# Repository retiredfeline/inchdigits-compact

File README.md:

# 1 inch tall 4 digit 7 segment display driven by TM1637 - compact version

These are the Kicad design files for my Hackaday project [Inch Digits](https://hackaday.io/project/169179-inch-digits)

## Versioning

November 2022

## Notes

## Authors

* **Ken Yap**

## License

See the [LICENSE](LICENSE.md) file for license rights and limitations (MIT).

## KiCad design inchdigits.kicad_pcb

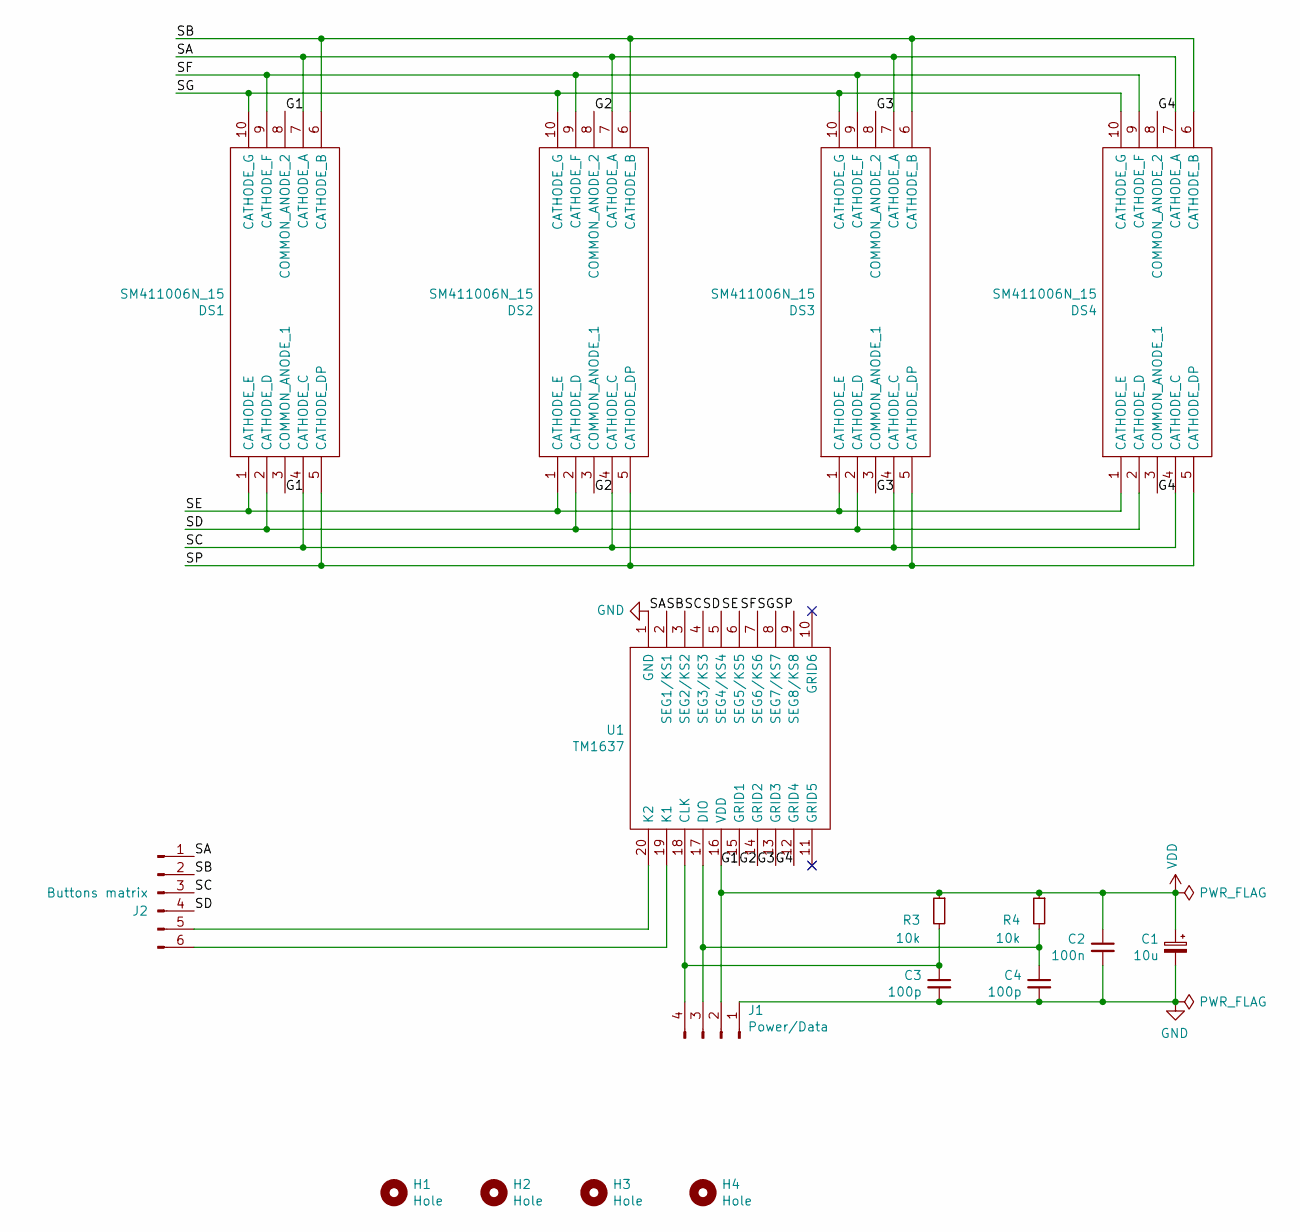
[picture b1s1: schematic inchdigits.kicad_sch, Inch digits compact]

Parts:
C1: 10u; C_0805_2012Metric_Pad1.18x1.45mm_HandSolder
C2: 100n; C_0805_2012Metric_Pad1.18x1.45mm_HandSolder
C3, C4: 100p; C_0805_2012Metric_Pad1.18x1.45mm_HandSolder
DS1, DS2, DS3, DS4: SM411006N_15; DIPS3048W51P254L2400H1075Q10N; Manufacturer_Part_Number SM411006N/15
H1, H2, H3, H4: Hole; MountingHole_3.5mm_Pad
J1: Power/Data; PinHeader_1x04_P2.54mm_Horizontal
J2: Buttons matrix; PinHeader_1x06_P2.54mm_Horizontal
R3, R4: 10k; R_0805_2012Metric_Pad1.20x1.40mm_HandSolder
U1: TM1637; SO-20_12.8x7.5mm_P1.27mm; Manufacturer_Part_Number TM1637

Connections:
/G1: DS1.3 (COMMON_ANODE_1), DS1.8 (COMMON_ANODE_2), U1.15 (GRID1)
/G2: DS2.3 (COMMON_ANODE_1), DS2.8 (COMMON_ANODE_2), U1.14 (GRID2)
/G3: DS3.3 (COMMON_ANODE_1), DS3.8 (COMMON_ANODE_2), U1.13 (GRID3)
/G4: DS4.3 (COMMON_ANODE_1), DS4.8 (COMMON_ANODE_2), U1.12 (GRID4)
/SA: DS1.7 (CATHODE_A), DS2.7 (CATHODE_A), DS3.7 (CATHODE_A), DS4.7 (CATHODE_A), J2.1, U1.2 (SEG1/KS1)
/SB: DS1.6 (CATHODE_B), DS2.6 (CATHODE_B), DS3.6 (CATHODE_B), DS4.6 (CATHODE_B), J2.2, U1.3 (SEG2/KS2)
/SC: DS1.4 (CATHODE_C), DS2.4 (CATHODE_C), DS3.4 (CATHODE_C), DS4.4 (CATHODE_C), J2.3, U1.4 (SEG3/KS3)
/SD: DS1.2 (CATHODE_D), DS2.2 (CATHODE_D), DS3.2 (CATHODE_D), DS4.2 (CATHODE_D), J2.4, U1.5 (SEG4/KS4)
/SE: DS1.1 (CATHODE_E), DS2.1 (CATHODE_E), DS3.1 (CATHODE_E), DS4.1 (CATHODE_E), U1.6 (SEG5/KS5)
/SF: DS1.9 (CATHODE_F), DS2.9 (CATHODE_F), DS3.9 (CATHODE_F), DS4.9 (CATHODE_F), U1.7 (SEG6/KS6)
/SG: DS1.10 (CATHODE_G), DS2.10 (CATHODE_G), DS3.10 (CATHODE_G), DS4.10 (CATHODE_G), U1.8 (SEG7/KS7)
/SP: DS1.5 (CATHODE_DP), DS2.5 (CATHODE_DP), DS3.5 (CATHODE_DP), DS4.5 (CATHODE_DP), U1.9 (SEG8/KS8)
GND: C1.2, C2.2, C3.2, C4.2, J1.1, U1.1 (GND)
unnamed: C4.1, J1.3, R4.2, U1.17 (DIO)
unnamed: C3.1, J1.4, R3.2, U1.18 (CLK)
unnamed: J2.5, U1.20 (K2)
unnamed: J2.6, U1.19 (K1)
VDD: C1.1, C2.1, J1.2, R3.1, R4.1, U1.16 (VDD)

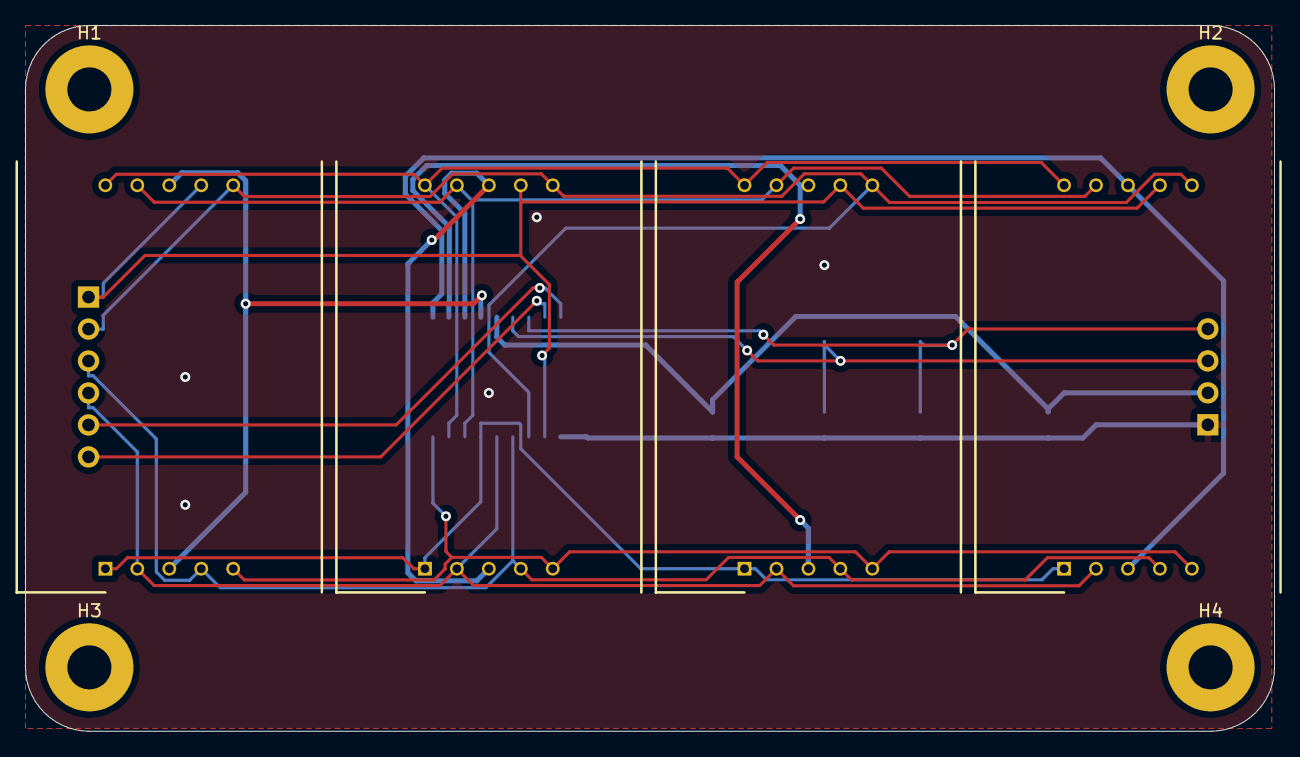
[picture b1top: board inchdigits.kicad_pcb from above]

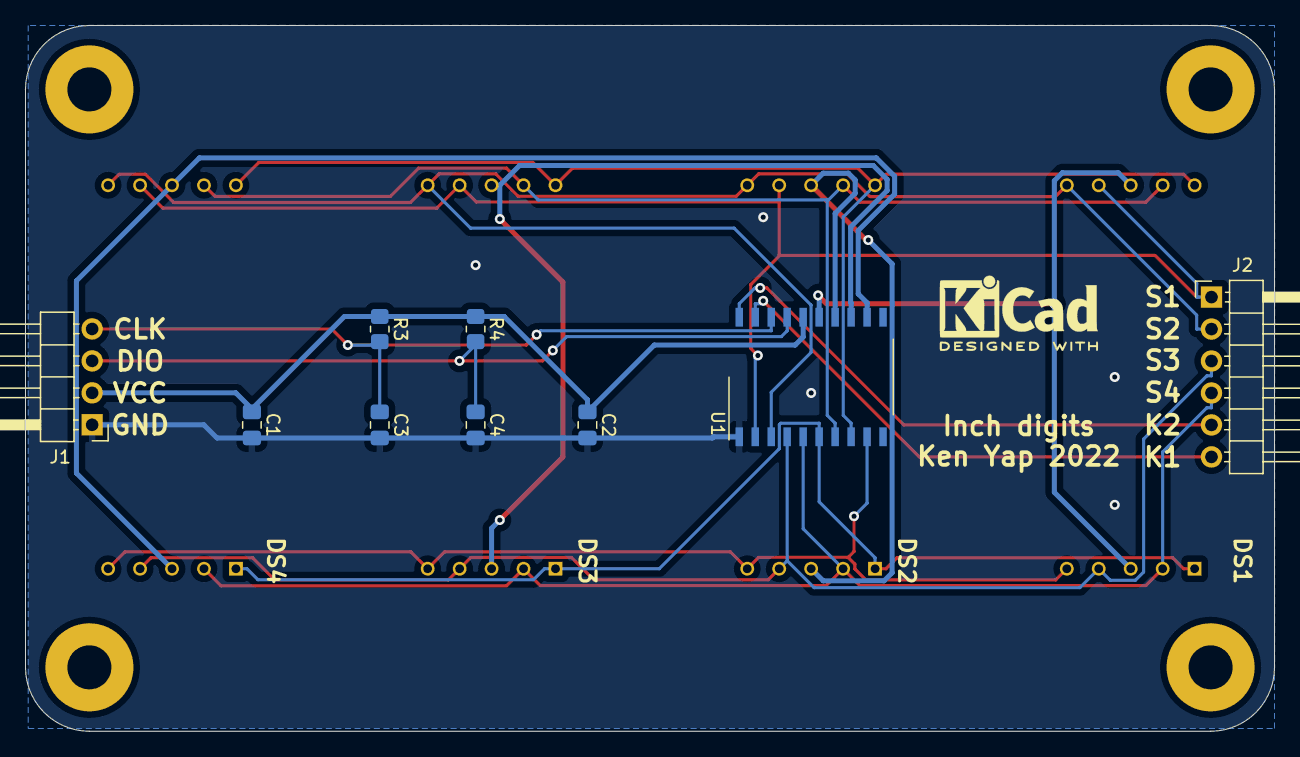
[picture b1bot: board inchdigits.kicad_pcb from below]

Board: 2 copper layers, 99.3 x 56.1 mm, 17 parts (9 on the bottom side), 18 nets.

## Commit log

2022-11-13 Initial release
2024-06-21 Update to KiCad 7, small tweaks
